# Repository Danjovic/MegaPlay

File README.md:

# MegaPlay
Sega Genesis/Megadrive controller adapter with keypad emulation for Atari 5200

 This adapter lets you play Atari 5200 using a 6 button Sega Genesis controller yet providing full keypad control.
 
  The circuit is built around an Arduino Nano and two analog multiplexers.
  
  Interface with analog joystick is borrowed from "Low Priced MasterPlay clone adapter" and uses two resistors and a capacitor on each axis to convert the digital directionals into equivalent charging time for minimum, medium and maximum position on each axis.

  Keypad presses are emulated by activating a pair of analog multiplexers. Only 1 (one) keypress can be simulated at a time. 
  When there is no key pressed the "output" multiplexer is inhibited. 
  
  Buttons are mapped as follows:

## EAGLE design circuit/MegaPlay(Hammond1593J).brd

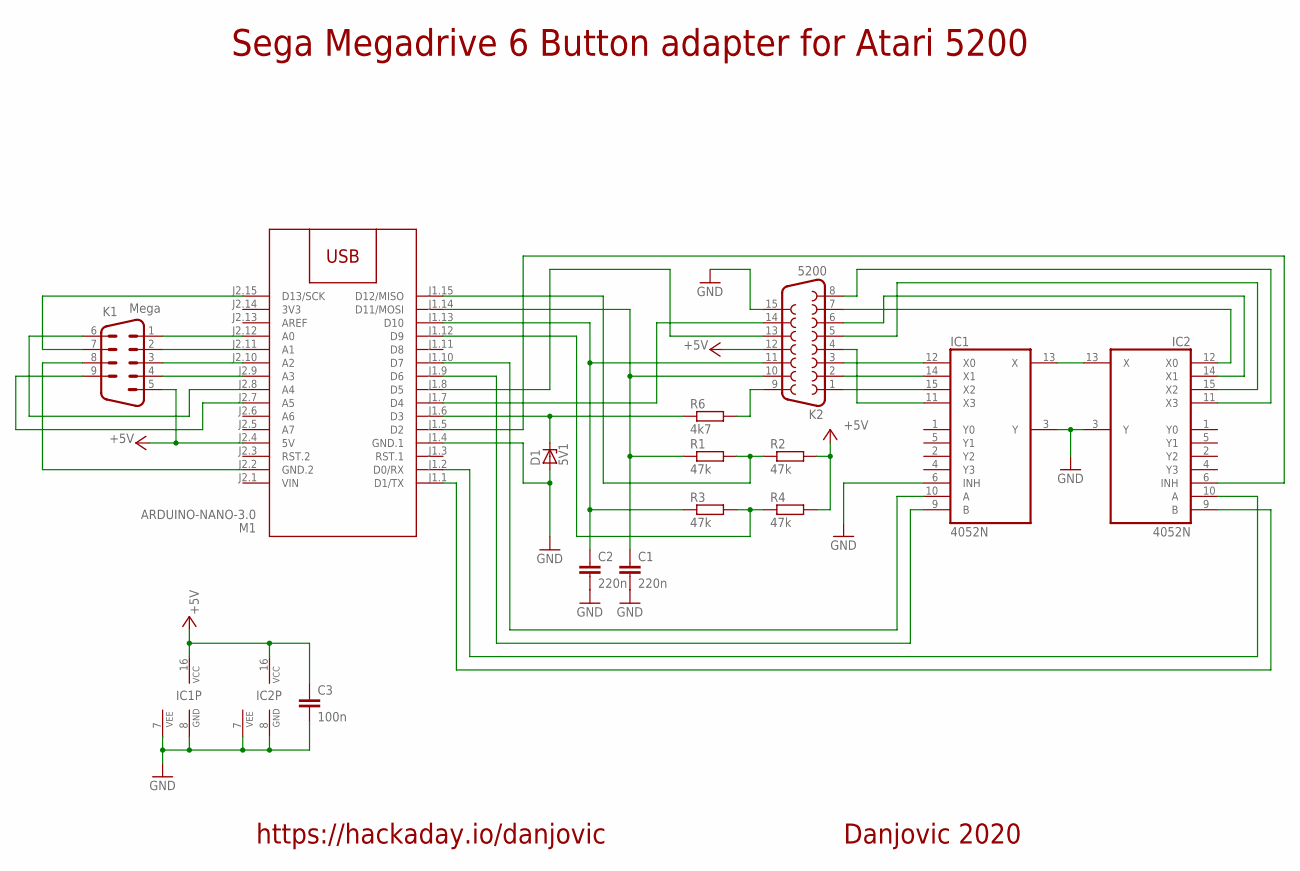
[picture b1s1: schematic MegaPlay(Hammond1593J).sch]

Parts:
C1, C2: 220n; C050-025X075
C3: 100n; C050-024X044
D1: 5V1; ZDIO-7.5
IC1, IC2: 4052N; DIL16
K1: Mega; M09H
K2: 5200; F15H
M1: ARDUINO-NANO-3.0
R1, R2, R3, R4: 47k; 0204/7
R6: 4k7; 0204/7

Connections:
3V3: M1.J2.14 (3V3)
+5V: C3.1, IC1.16 (VCC), IC2.16 (VCC), K1.5, K2.12, M1.J2.4 (5V), R2.2, R4.2
GND: C1.2, C2.2, C3.2, D1.A, IC1.3 (Y), IC1.6 (INH), IC1.7 (VEE), IC1.8 (GND), IC2.3 (Y), IC2.7 (VEE), IC2.8 (GND), K2.15, M1.J1.4 (GND.1)
unnamed: M1.J1.12 (D9), R3.2, R4.1
unnamed: IC1.15 (X2), K2.1
unnamed: IC1.13 (X), IC2.13 (X)
unnamed: IC1.14 (X1), K2.2
unnamed: IC1.12 (X0), K2.3
unnamed: IC1.11 (X3), K2.4
unnamed: IC2.15 (X2), K2.5
unnamed: IC2.14 (X1), K2.6
unnamed: IC2.12 (X0), K2.7
unnamed: K1.1, M1.J2.12 (A0)
unnamed: C1.1, K2.10, M1.J1.14 (D11/MOSI), R1.1
unnamed: M1.J1.15 (D12/MISO), R1.2, R2.1
unnamed: IC2.11 (X3), K2.8
unnamed: C2.1, K2.11, M1.J1.13 (D10), R3.1
unnamed: K2.13, M1.J1.8 (D5)
unnamed: K1.2, M1.J2.11 (A1)
unnamed: K1.3, M1.J2.10 (A2)
unnamed: K1.4, M1.J2.9 (A3)
unnamed: K1.7, M1.J2.15 (D13/SCK)
unnamed: K1.6, M1.J2.8 (A4)
unnamed: K1.9, M1.J2.7 (A5)
unnamed: K1.8, M1.J2.2 (GND.2)
unnamed: D1.C, M1.J1.6 (D3), R6.1
unnamed: IC2.6 (INH), M1.J1.5 (D2)
unnamed: K2.9, R6.2
unnamed: IC2.10 (A), M1.J1.2 (D0/RX)
unnamed: IC2.9 (B), M1.J1.1 (D1/TX)
unnamed: K2.14, M1.J1.7 (D4)
unnamed: IC1.10 (A), M1.J1.10 (D7)
unnamed: IC1.9 (B), M1.J1.9 (D6)
VIN: M1.J2.1 (VIN)

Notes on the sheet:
Sega Megadrive 6 Button adapter for Atari 5200
Danjovic 2020
https://hackaday.io/danjovic

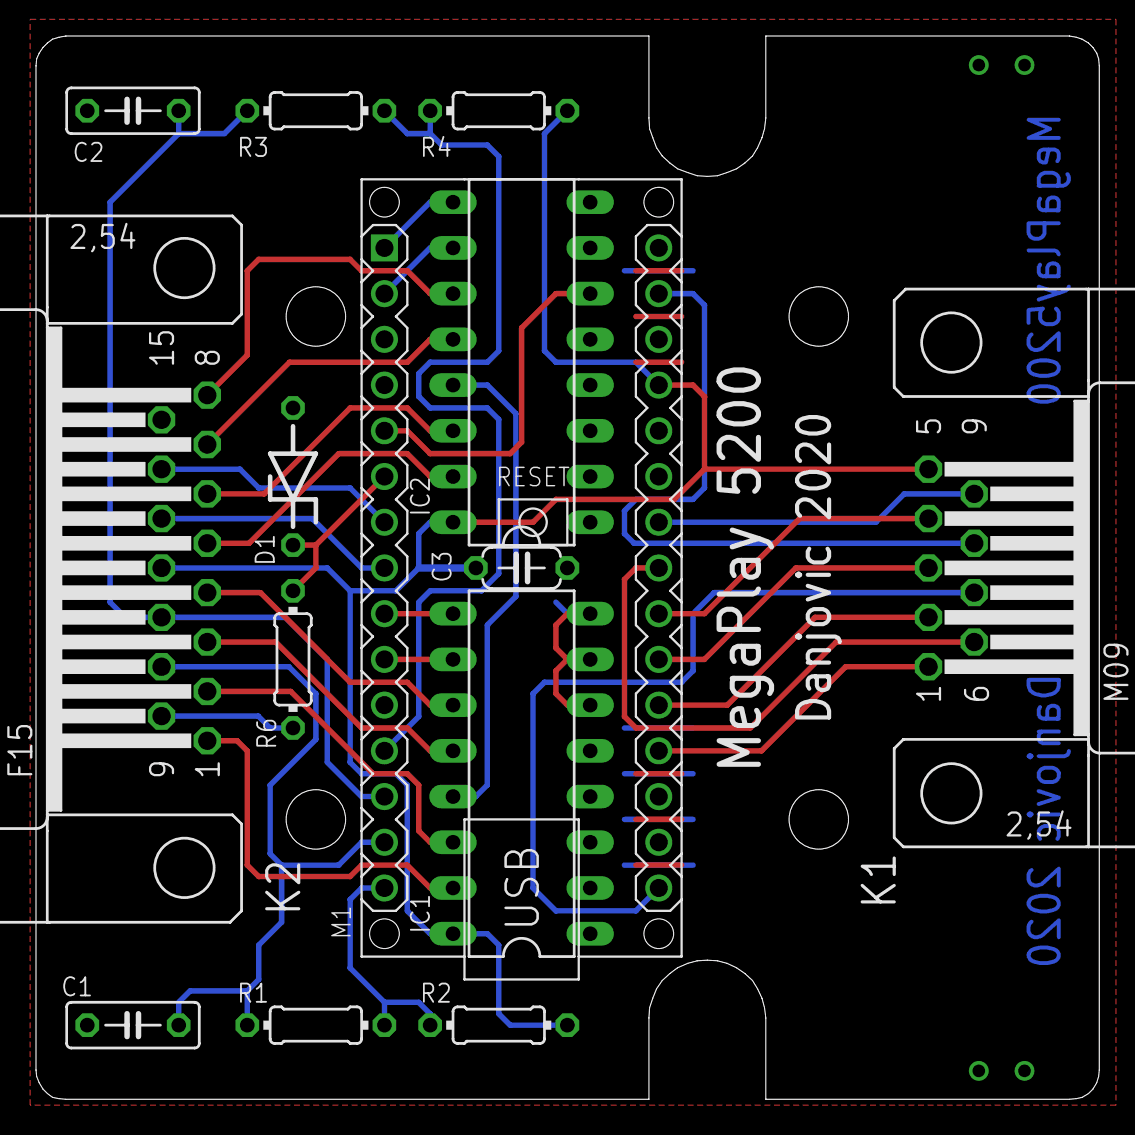
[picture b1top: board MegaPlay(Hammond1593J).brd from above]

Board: 2 copper layers, 59.1 x 59.1 mm, 15 parts (0 on the bottom side), 32 nets.

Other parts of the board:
U$1: 1593J

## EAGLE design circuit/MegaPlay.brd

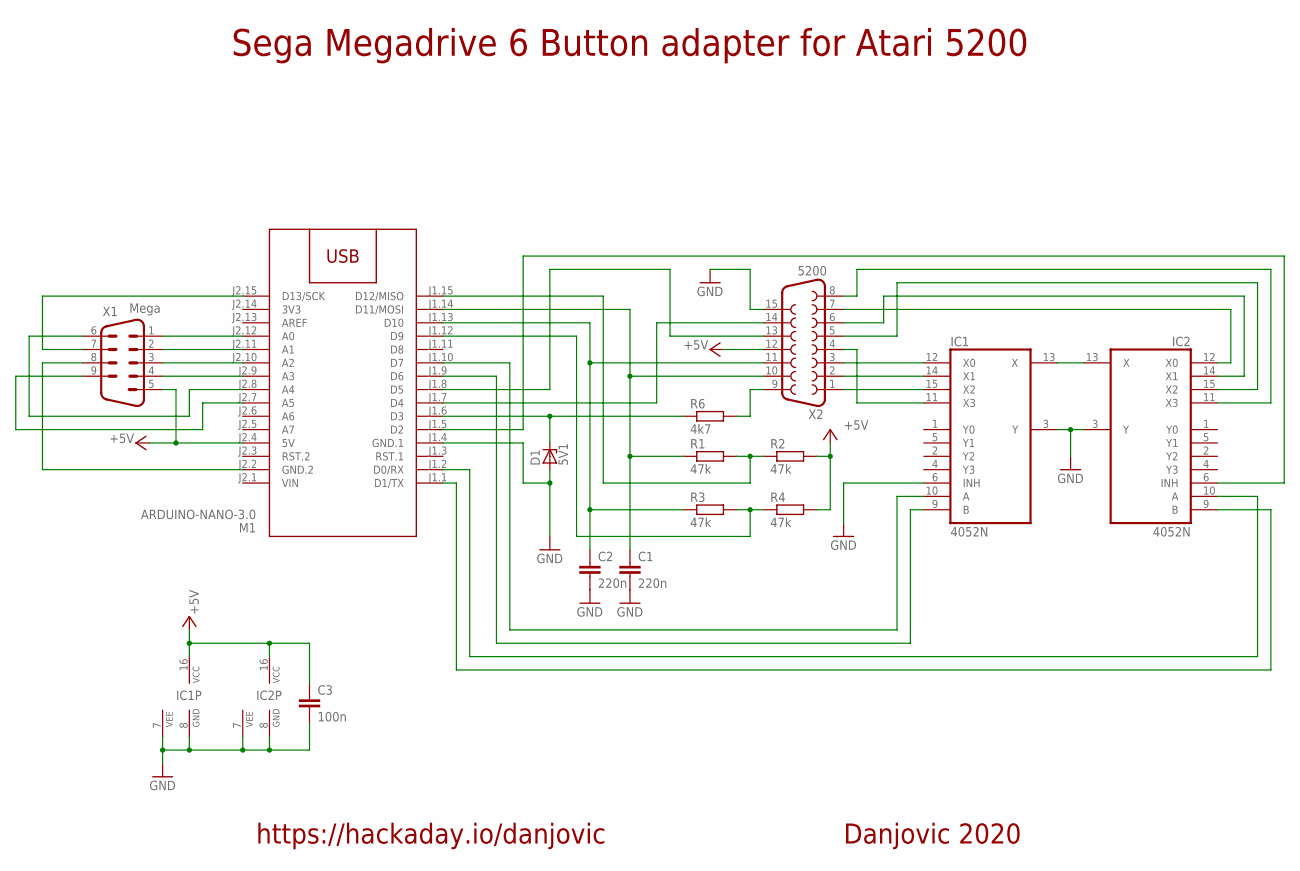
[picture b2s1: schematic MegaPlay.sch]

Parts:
C1, C2: 220n; C050-025X075
C3: 100n; C050-024X044
D1: 5V1; ZDIO-7.5
IC1, IC2: 4052N; DIL16
M1: ARDUINO-NANO-3.0
R1, R2, R3, R4: 47k; 0204/7
R6: 4k7; 0204/7
X1: Mega; M09D
X2: 5200; F15D

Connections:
3V3: M1.J2.14 (3V3)
+5V: C3.1, IC1.16 (VCC), IC2.16 (VCC), M1.J2.4 (5V), R2.2, R4.2, X1.5, X2.12
GND: C1.2, C2.2, C3.2, D1.A, IC1.3 (Y), IC1.6 (INH), IC1.7 (VEE), IC1.8 (GND), IC2.3 (Y), IC2.7 (VEE), IC2.8 (GND), M1.J1.4 (GND.1), X2.15
unnamed: M1.J1.12 (D9), R3.2, R4.1
unnamed: IC1.15 (X2), X2.1
unnamed: IC1.13 (X), IC2.13 (X)
unnamed: IC1.14 (X1), X2.2
unnamed: IC1.12 (X0), X2.3
unnamed: IC1.11 (X3), X2.4
unnamed: IC2.15 (X2), X2.5
unnamed: IC2.14 (X1), X2.6
unnamed: IC2.12 (X0), X2.7
unnamed: M1.J2.12 (A0), X1.1
unnamed: C1.1, M1.J1.14 (D11/MOSI), R1.1, X2.10
unnamed: M1.J1.15 (D12/MISO), R1.2, R2.1
unnamed: IC2.11 (X3), X2.8
unnamed: C2.1, M1.J1.13 (D10), R3.1, X2.11
unnamed: M1.J1.8 (D5), X2.13
unnamed: M1.J2.11 (A1), X1.2
unnamed: M1.J2.10 (A2), X1.3
unnamed: M1.J2.9 (A3), X1.4
unnamed: M1.J2.15 (D13/SCK), X1.7
unnamed: M1.J2.8 (A4), X1.6
unnamed: M1.J2.7 (A5), X1.9
unnamed: M1.J2.2 (GND.2), X1.8
unnamed: D1.C, M1.J1.6 (D3), R6.1
unnamed: IC2.6 (INH), M1.J1.5 (D2)
unnamed: R6.2, X2.9
unnamed: IC2.10 (A), M1.J1.2 (D0/RX)
unnamed: IC2.9 (B), M1.J1.1 (D1/TX)
unnamed: M1.J1.7 (D4), X2.14
unnamed: IC1.10 (A), M1.J1.10 (D7)
unnamed: IC1.9 (B), M1.J1.9 (D6)
VIN: M1.J2.1 (VIN)

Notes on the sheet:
Sega Megadrive 6 Button adapter for Atari 5200
Danjovic 2020
https://hackaday.io/danjovic

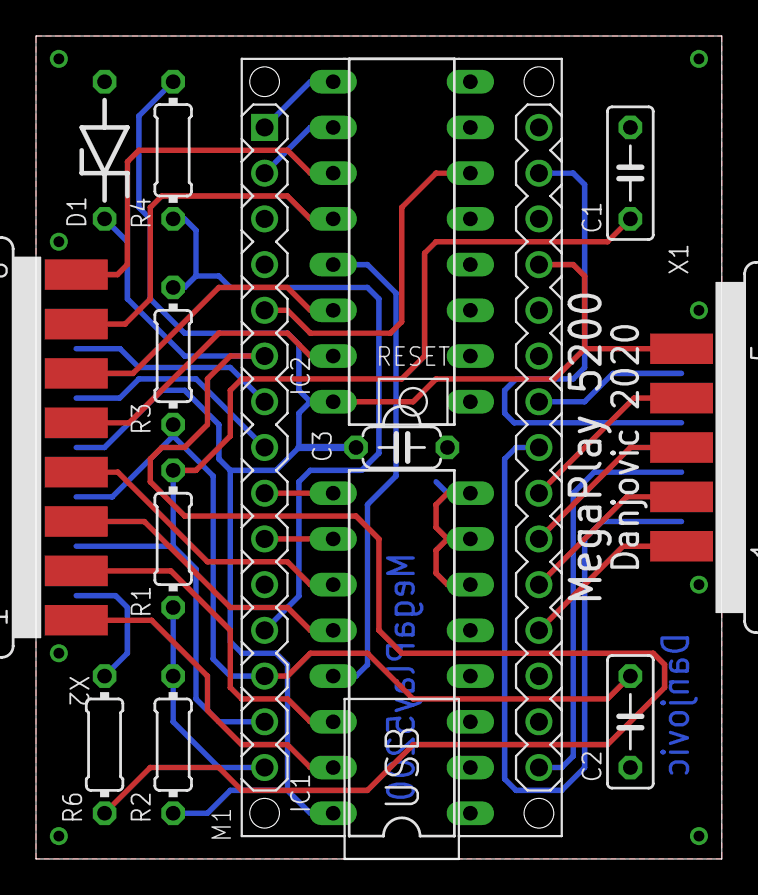
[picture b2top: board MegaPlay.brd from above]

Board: 2 copper layers, 38.1 x 45.7 mm, 14 parts (0 on the bottom side), 32 nets.

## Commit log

2020-01-24 Added files
    Files added only. Not tested code.
2020-02-04 Added Eagle intermediary files to gitignore
2020-02-10 Upload of image
2020-02-10 Work in progress, not a release
2020-03-01 Code update. Keypad emulation OK.
2020-03-01 Added decoupling capacitor to Analog Switches power supply.
2020-03-02 Added support for 6 button controller without MODE key
2020-03-15 corrected button assignment table in comments
2020-03-15 Removed deprecated MODE key modifier functionality
2020-03-15 remove last reference to MODE key
2020-10-01 Added PCB version for Hammond 1593J box

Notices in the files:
parts and their libraries:
diy-modules: Released under the Creative Commons Attribution 4.0 International License: http://creativecommons.org/licenses/by/4.0
SparkFun-Aesthetics: Licensing: Creative Commons ShareAlike 4.0 International - https://creativecommons.org/licenses/by-sa/4.0
